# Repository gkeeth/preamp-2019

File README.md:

# preamp-2019

Balanced input & output preamplifier with volume and balance controls.

Based on preamps designed by Doug Self (see Small Signal Audio Design by Douglas Self)

The preamp is split over several PCBs, with a kicad project for each:
1. balanced_amplifier: balanced amplifier with volume/balance controls
2. power_supply: power supplies for
    - positive analog rail
    - negative analog rail
    - digital/relay rail
3. input_output_board: board with input/output jacks and relays to select the desired input
4. front_panel_board: board with input selection switch and headphone/main output switch
5. headphone_amp: a very basic headphone amplifier that converts the balanced
   output of the balanced_amplifier board to an unbalanced signal, and buffers it

This work is licensed under a [Creative Commons Attribution-ShareAlike 4.0
International License][cc-by-sa].

[![CC BY-SA 4.0][cc-by-sa-image]][cc-by-sa]

[cc-by-sa]: http://creativecommons.org/licenses/by-sa/4.0/
[cc-by-sa-image]: https://licensebuttons.net/l/by-sa/4.0/88x31.png
[cc-by-sa-shield]: https://img.shields.io/badge/License-CC%20BY--SA%204.0-lightgrey.svg

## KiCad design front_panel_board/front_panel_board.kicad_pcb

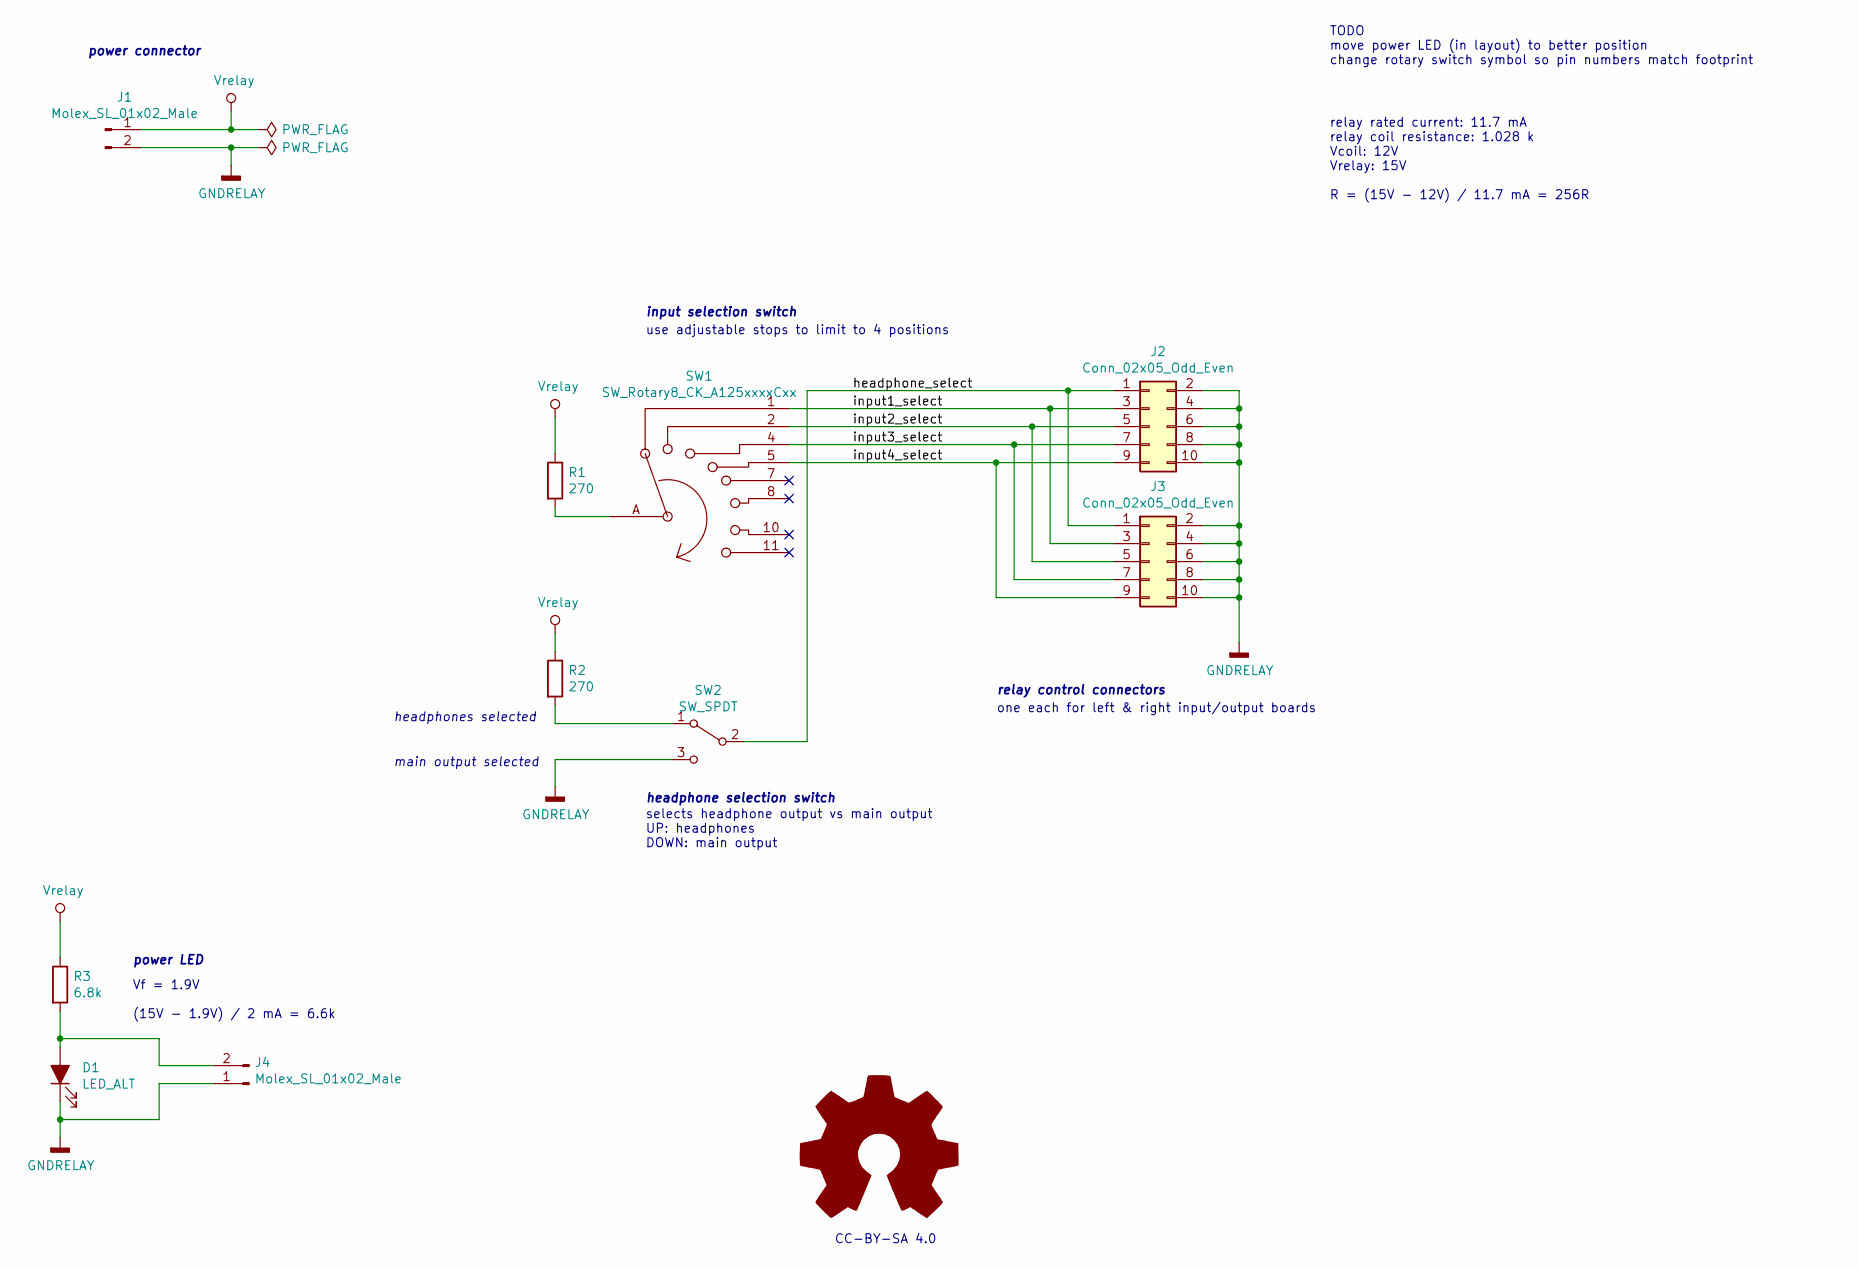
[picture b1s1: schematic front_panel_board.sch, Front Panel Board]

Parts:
D1: LED_ALT; LED_D5.0mm; Manufacturer PN WP7113LGD
J1, J4: Molex_SL_01x02_Male; Molex_SL_A-70543-0001_1x02_P2.54mm_Vertical; Manufacturer PN 0705430001
J2, J3: Conn_02x05_Odd_Even; Molex_C-Grid_70246-1001_2x05_P2.54mm_Vertical; Manufacturer PN 0702461001
R1, R2: 270; R_0805_2012Metric_Pad1.15x1.40mm_HandSolder; Manufacturer PN RT0805FRE07270RL
R3: 6.8k; R_0603_1608Metric_Pad1.05x0.95mm_HandSolder; Manufacturer PN YAG5968CT-ND
SW1: SW_Rotary8_CK_A125xxxxCxx; Manufacturer PN A12505RNCQ
SW2: SW_SPDT; SW_Toggle_SPDT_NKK_M201xxxx03; Manufacturer PN M2012SS1W03

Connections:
/headphone_select: J2.1, J3.1, SW2.2 (B)
/input1_select: J2.3, J3.3, SW1.1
/input2_select: J2.5, J3.5, SW1.2
/input3_select: J2.7, J3.7, SW1.4
/input4_select: J2.9, J3.9, SW1.5
GNDRELAY: D1.1 (K), J1.2, J2.2, J2.4, J2.6, J2.8, J2.10, J3.2, J3.4, J3.6, J3.8, J3.10, J4.1, SW2.3 (C)
unnamed: D1.2 (A), J4.2, R3.2
unnamed: R1.2, SW1.A
unnamed: R2.2, SW2.1 (A)
Vrelay: J1.1, R1.1, R2.1, R3.1

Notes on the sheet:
selects headphone output vs main output UP: headphones DOWN: main output
headphone selection switch
input selection switch
power connector
power LED
use adjustable stops to limit to 4 positions
relay rated current: 11.7 mA relay coil resistance: 1.028 k Vcoil: 12V Vrelay: 15V R = (15V - 12V) / 11.7 mA = 256R
Vf = 1.9V (15V - 1.9V) / 2 mA = 6.6k
TODO move power LED (in layout) to better position change rotary switch symbol so pin numbers match footprint
CC-BY-SA 4.0
relay control connectors
one each for left & right input/output boards
headphones selected
main output selected

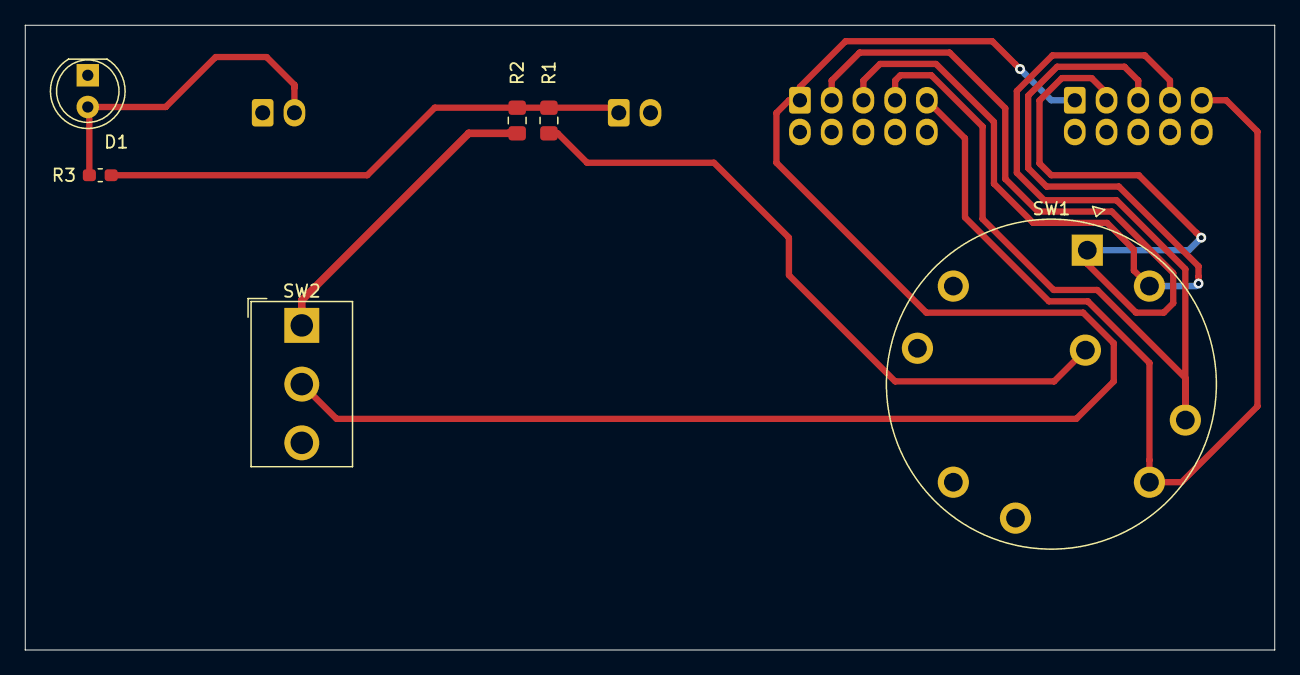
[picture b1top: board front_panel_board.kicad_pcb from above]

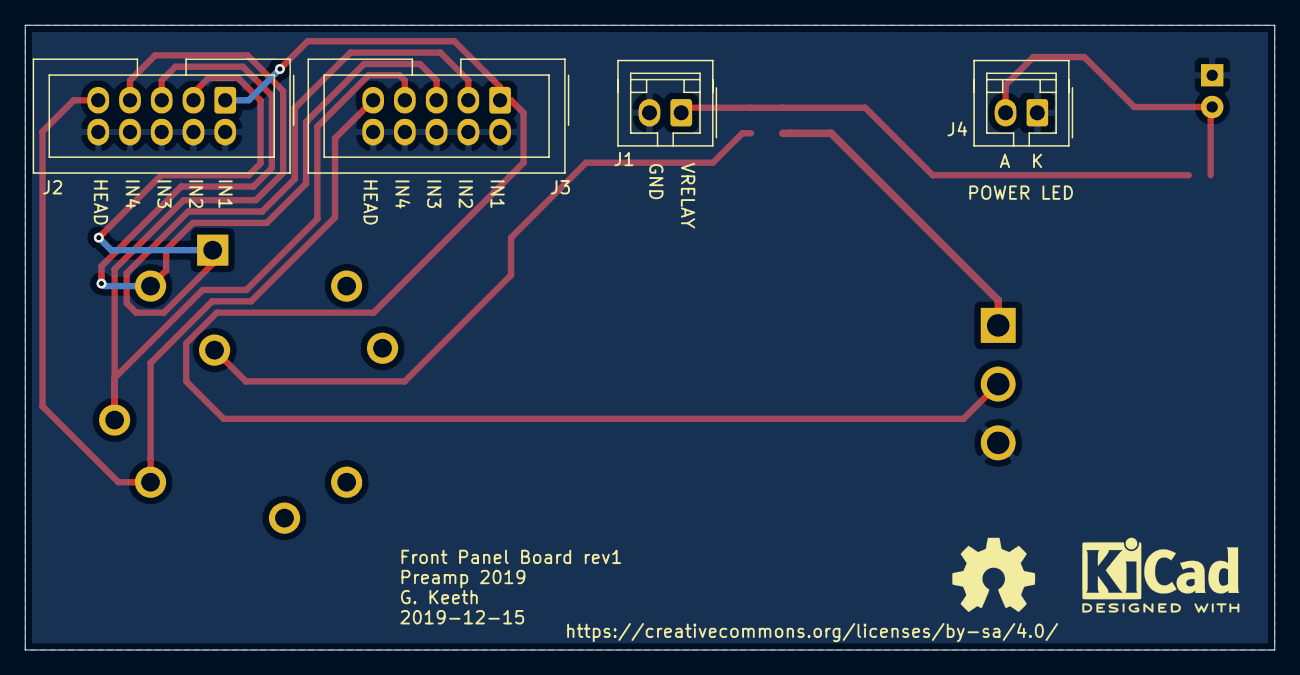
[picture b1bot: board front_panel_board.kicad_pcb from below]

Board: 2 copper layers, 100.0 x 50.0 mm, 10 parts (4 on the bottom side), 10 nets.

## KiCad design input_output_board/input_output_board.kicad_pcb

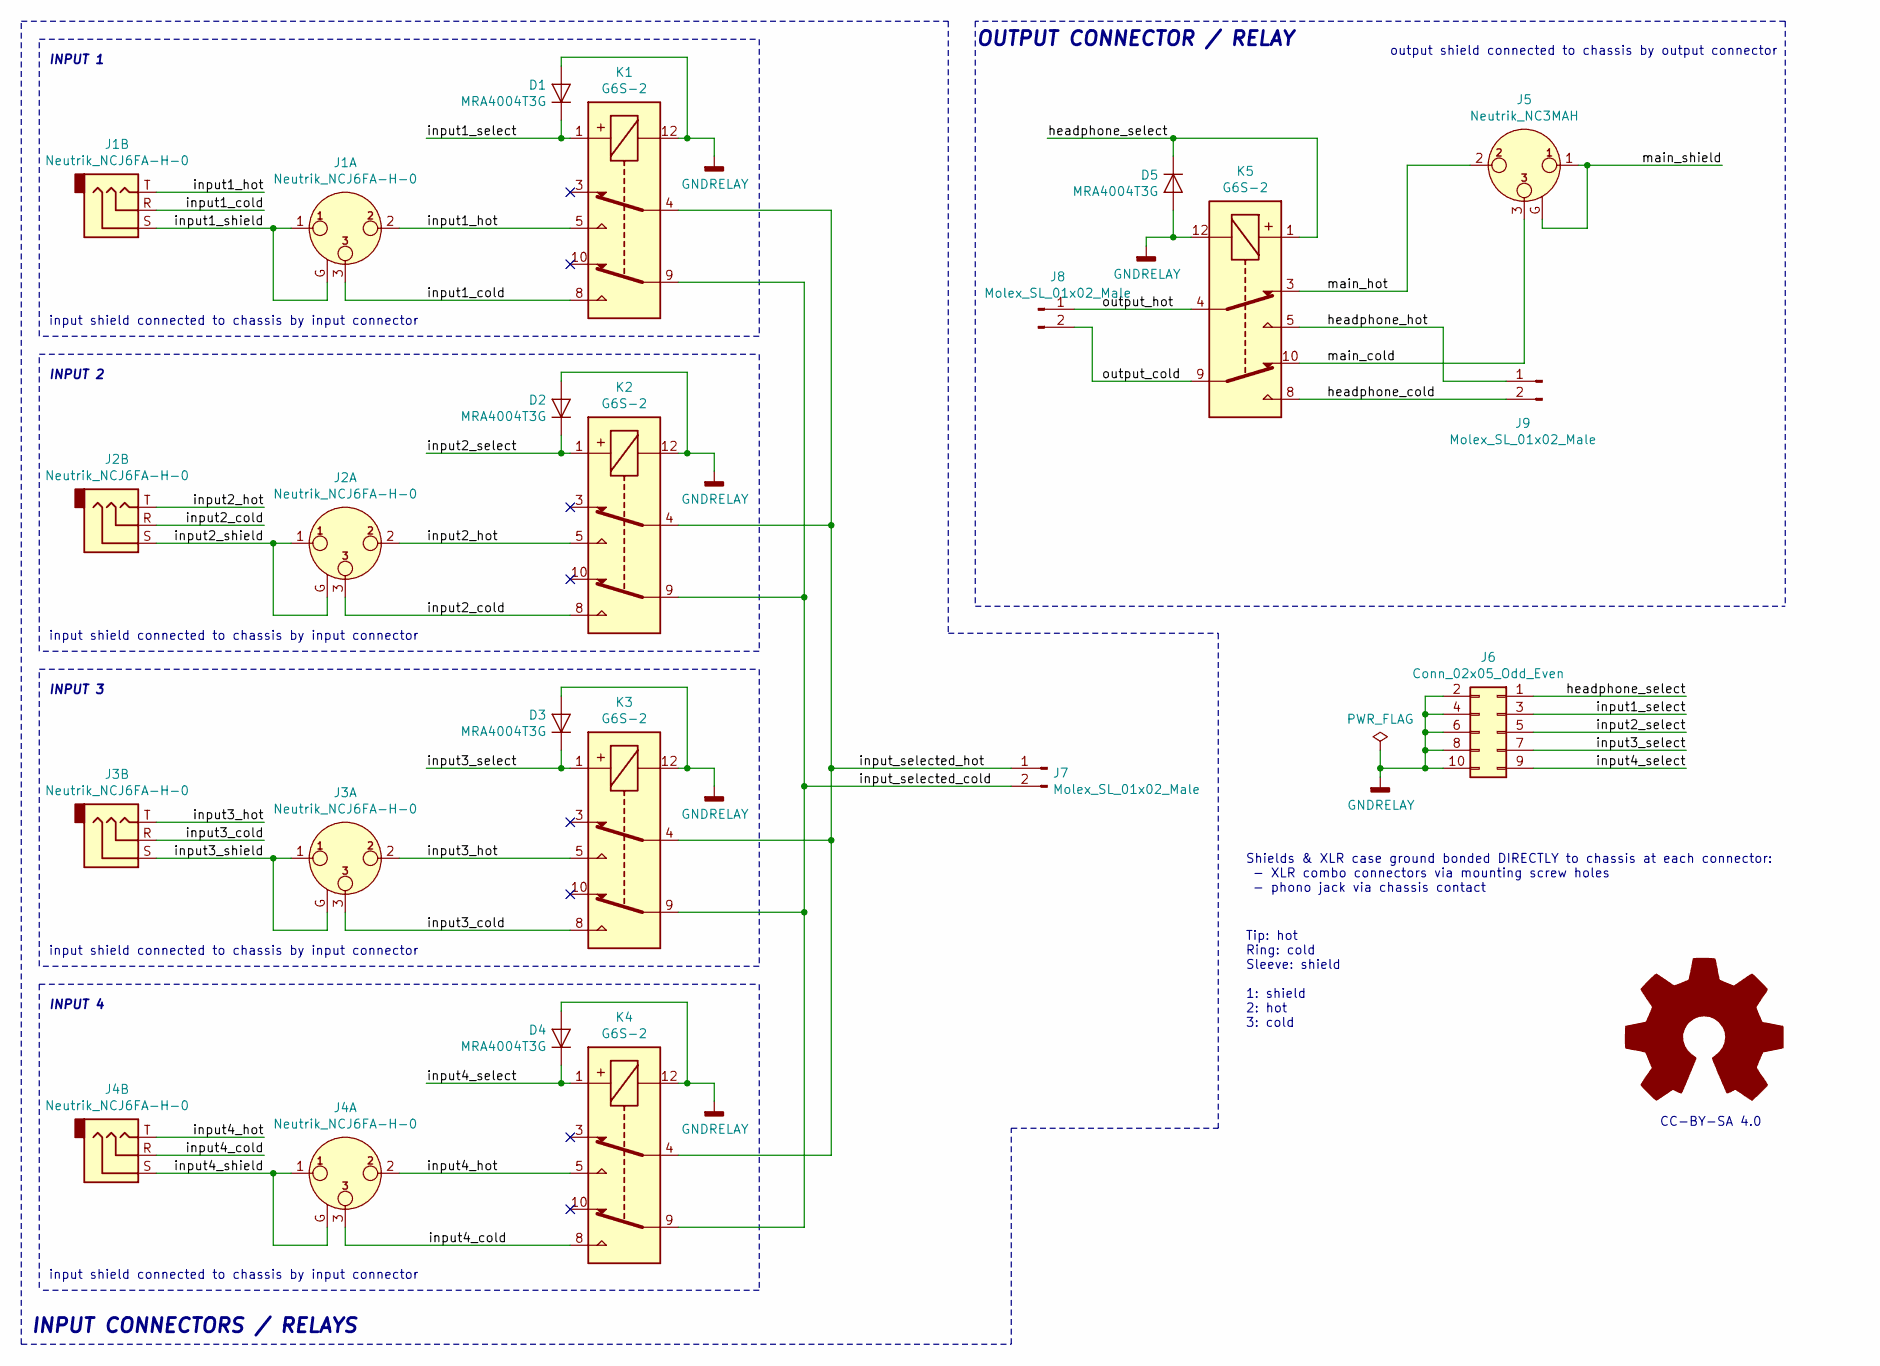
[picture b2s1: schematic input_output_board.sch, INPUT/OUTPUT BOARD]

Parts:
D1, D2, D3, D4, D5: MRA4004T3G; D_SMA; Manufacturer PN MRA4004T3G
J1, J2, J3, J4: Neutrik_NCJ6FA-H-0; Jack_XLR-6.35mm_Neutrik_NCJ6FA-H-0_Horizontal; Manufacturer PN NCJ6FA-H-0
J5: Neutrik_NC3MAH; Jack_XLR_Neutrik_NC3MAH_Horizontal; Manufacturer PN NC3MAH
J6: Conn_02x05_Odd_Even; Molex_C-Grid_70247-10xx_2x05_P2.54mm_Horizontal; Manufacturer PN 0702461001
J7, J8, J9: Molex_SL_01x02_Male; Molex_SL_A-70553-0001_1x02_P2.54mm_Horizontal; Manufacturer PN 0705430001
K1, K2, K3, K4, K5: G6S-2; Relay_DPDT_Omron_G6S-2F; Manufacturer PN G6S-2F DC12

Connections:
/headphone_cold: J9.2, K5.8
/headphone_hot: J9.1, K5.5
/headphone_select: D5.1 (K), J6.1, K5.1
/input1_cold: J1.3, J1.R, K1.8
/input1_hot: J1.2, J1.T, K1.5
/input1_select: D1.1 (K), J6.3, K1.1
/input1_shield: J1.1, J1.G, J1.S
/input2_cold: J2.3, J2.R, K2.8
/input2_hot: J2.2, J2.T, K2.5
/input2_select: D2.1 (K), J6.5, K2.1
/input2_shield: J2.1, J2.G, J2.S
/input3_cold: J3.3, J3.R, K3.8
/input3_hot: J3.2, J3.T, K3.5
/input3_select: D3.1 (K), J6.7, K3.1
/input3_shield: J3.1, J3.G, J3.S
/input4_cold: J4.3, J4.R, K4.8
/input4_hot: J4.2, J4.T, K4.5
/input4_select: D4.1 (K), J6.9, K4.1
/input4_shield: J4.1, J4.G, J4.S
/input_selected_cold: J7.2, K1.9, K2.9, K3.9, K4.9
/input_selected_hot: J7.1, K1.4, K2.4, K3.4, K4.4
/main_cold: J5.3, K5.10
/main_hot: J5.2, K5.3
/main_shield: J5.1, J5.G
/output_cold: J8.2, K5.9
/output_hot: J8.1, K5.4
GNDRELAY: D1.2 (A), D2.2 (A), D3.2 (A), D4.2 (A), D5.2 (A), J6.2, J6.4, J6.6, J6.8, J6.10, K1.12, K2.12, K3.12, K4.12, K5.12

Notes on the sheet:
Tip: hot Ring: cold Sleeve: shield 1: shield 2: hot 3: cold
Shields & XLR case ground bonded DIRECTLY to chassis at each connector: - XLR combo connectors via mounting screw holes - phono jack via chassis contact
INPUT CONNECTORS / RELAYS
INPUT 1
INPUT 2
INPUT 3
INPUT 4
CC-BY-SA 4.0
input shield connected to chassis by input connector
output shield connected to chassis by output connector
OUTPUT CONNECTOR / RELAY

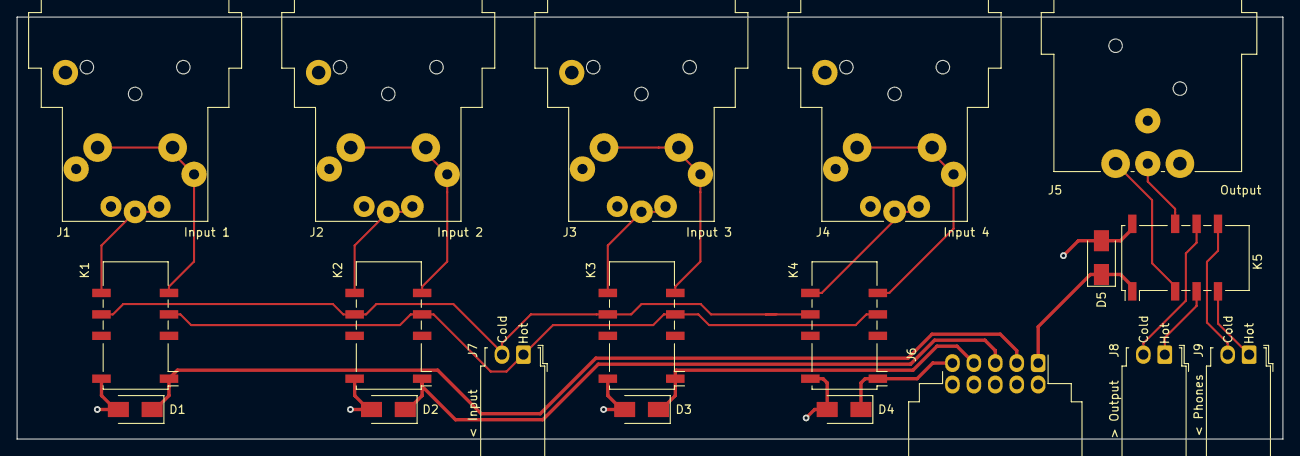
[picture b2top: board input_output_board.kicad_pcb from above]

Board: 2 copper layers, 150.0 x 50.0 mm, 19 parts (0 on the bottom side), 27 nets.

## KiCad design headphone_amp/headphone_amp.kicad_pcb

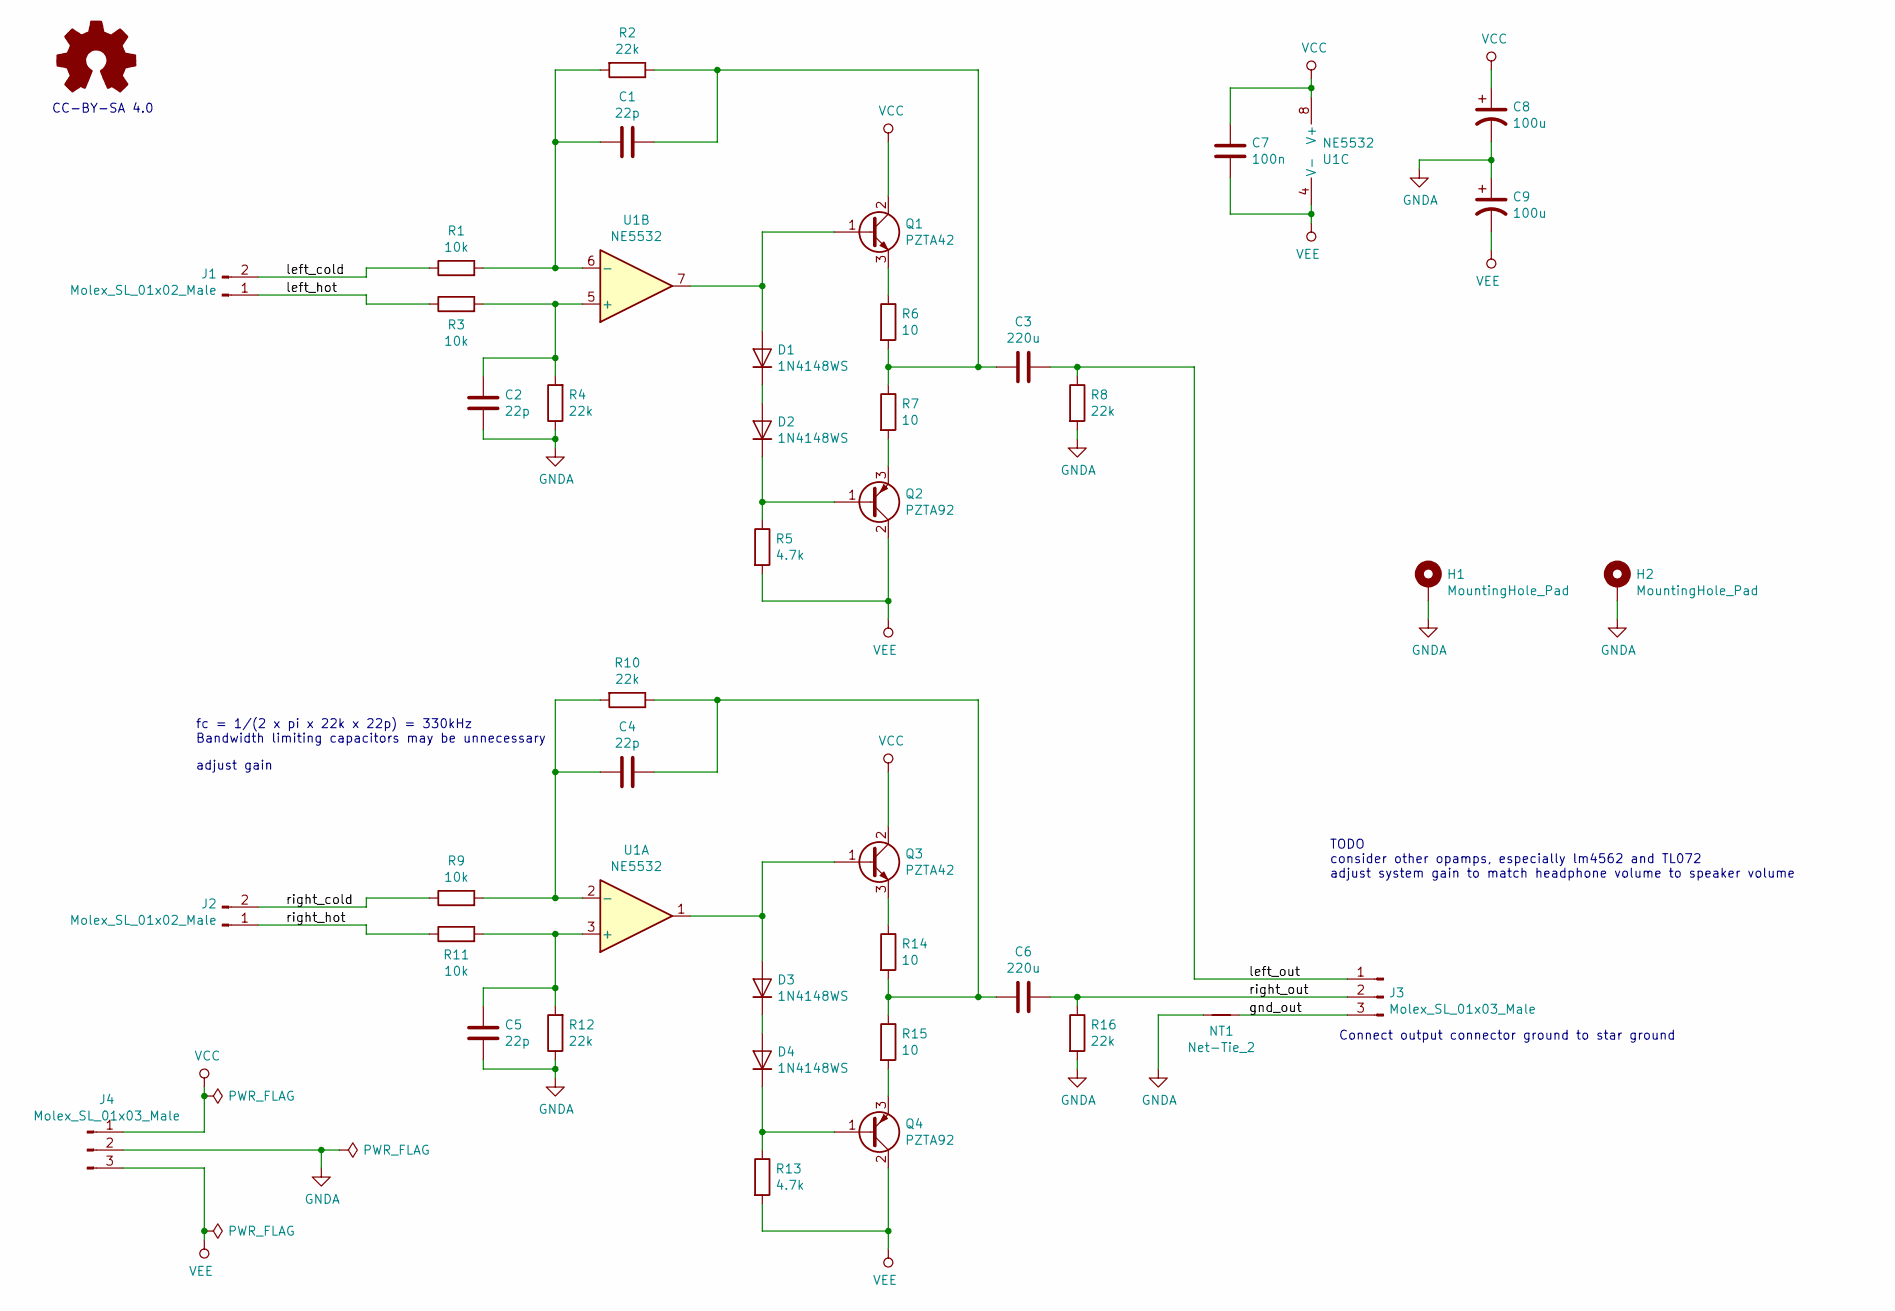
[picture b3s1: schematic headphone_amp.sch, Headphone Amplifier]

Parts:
C1, C2, C4, C5: 22p; C_0603_1608Metric_Pad1.05x0.95mm_HandSolder; Manufacturer PN C0603C220J5GAC7411
C3, C6: 220u; C_Radial_D12.5mm_H20.0mm_P5.00mm; Voltage Rating 35V; Manufacturer PN UVP1V221MHD
C7: 100n; C_0805_2012Metric_Pad1.15x1.40mm_HandSolder; Manufacturer PN GCM21BR72A104KA37K
C8, C9: 100u; CP_Radial_D6.3mm_P2.50mm; Voltage Rating 35V; Manufacturer PN UVR1V101MED
D1, D2, D3, D4: 1N4148WS; D_SOD-323; Manufacturer PN 1N4148WS
H1, H2: MountingHole_Pad; MountingHole_3.2mm_M3_Pad
J1, J2: Molex_SL_01x02_Male; Molex_SL_A-70553-0001_1x02_P2.54mm_Horizontal; Manufacturer PN 70553-0001
J3, J4: Molex_SL_01x03_Male; Molex_SL_A-70553-0002_1x03_P2.54mm_Horizontal; Manufacturer PN 70553-0002
NT1: Net-Tie_2; NetTie-2_SMD_Pad2.0mm
Q1, Q3: PZTA42; SOT-223-3_TabPin2; Manufacturer PN PZTA42T1G
Q2, Q4: PZTA92; SOT-223-3_TabPin2; Manufacturer PN PZTA92T1G
R1, R3, R9, R11: 10k; R_0603_1608Metric_Pad1.05x0.95mm_HandSolder; Manufacturer PN RT0603FRE0710KL
R2, R4, R8, R10, R12, R16: 22k; R_0603_1608Metric_Pad1.05x0.95mm_HandSolder; Manufacturer PN RT0603FRE1322KL
R5, R13: 4.7k; R_0603_1608Metric_Pad1.05x0.95mm_HandSolder; Manufacturer PN RT0603FRE074K7L
R6, R7, R14, R15: 10; R_0603_1608Metric_Pad1.05x0.95mm_HandSolder; Manufacturer PN RNCP0603FTD10R0
U1: NE5532; SOIC-8_3.9x4.9mm_P1.27mm; Manufacturer PN NE5532AD8R2G

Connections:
/gnd_out: J3.3, NT1.2
/left_cold: J1.2, R1.1
/left_hot: J1.1, R3.1
/left_out: C3.1, J3.1, R8.1
/right_cold: J2.2, R9.1
/right_hot: J2.1, R11.1
/right_out: C6.1, J3.2, R16.1
GNDA: C2.2, C5.2, C8.2, C9.1, H1.1, H2.1, J4.2, NT1.1, R4.1, R8.2, R12.1, R16.2
unnamed: C1.1, C3.2, R2.1, R6.2, R7.1
unnamed: C1.2, R1.2, R2.2, U1.6 (-)
unnamed: C2.1, R3.2, R4.2, U1.5 (+)
unnamed: C4.1, C6.2, R10.1, R14.2, R15.1
unnamed: C4.2, R9.2, R10.2, U1.2 (-)
unnamed: C5.1, R11.2, R12.2, U1.3 (+)
unnamed: D1.1 (K), D2.2 (A)
unnamed: D1.2 (A), Q1.1 (B), U1.7
unnamed: D2.1 (K), Q2.1 (B), R5.1
unnamed: D3.1 (K), D4.2 (A)
unnamed: D3.2 (A), Q3.1 (B), U1.1
unnamed: D4.1 (K), Q4.1 (B), R13.1
unnamed: Q1.3 (E), R6.1
unnamed: Q2.3 (E), R7.2
unnamed: Q3.3 (E), R14.1
unnamed: Q4.3 (E), R15.2
VCC: C7.1, C8.1, J4.1, Q1.2 (C), Q3.2 (C), U1.8 (V+)
VEE: C7.2, C9.2, J4.3, Q2.2 (C), Q4.2 (C), R5.2, R13.2, U1.4 (V-)

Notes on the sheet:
TODO consider other opamps, especially lm4562 and TL072 adjust system gain to match headphone volume to speaker volume
CC-BY-SA 4.0
fc = 1/(2 x pi x 22k x 22p) = 330kHz Bandwidth limiting capacitors may be unnecessary
Connect output connector ground to star ground
adjust gain

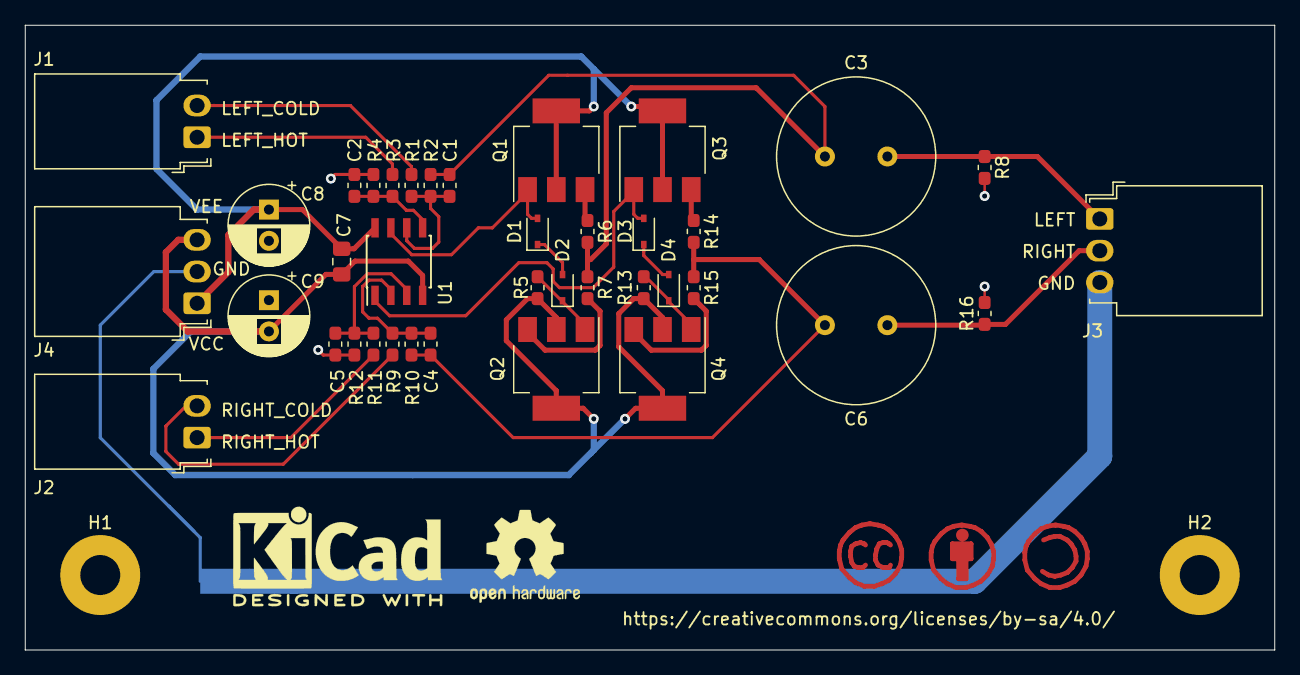
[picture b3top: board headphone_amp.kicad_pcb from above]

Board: 2 copper layers, 100.0 x 50.0 mm, 41 parts (1 on the bottom side), 26 nets.

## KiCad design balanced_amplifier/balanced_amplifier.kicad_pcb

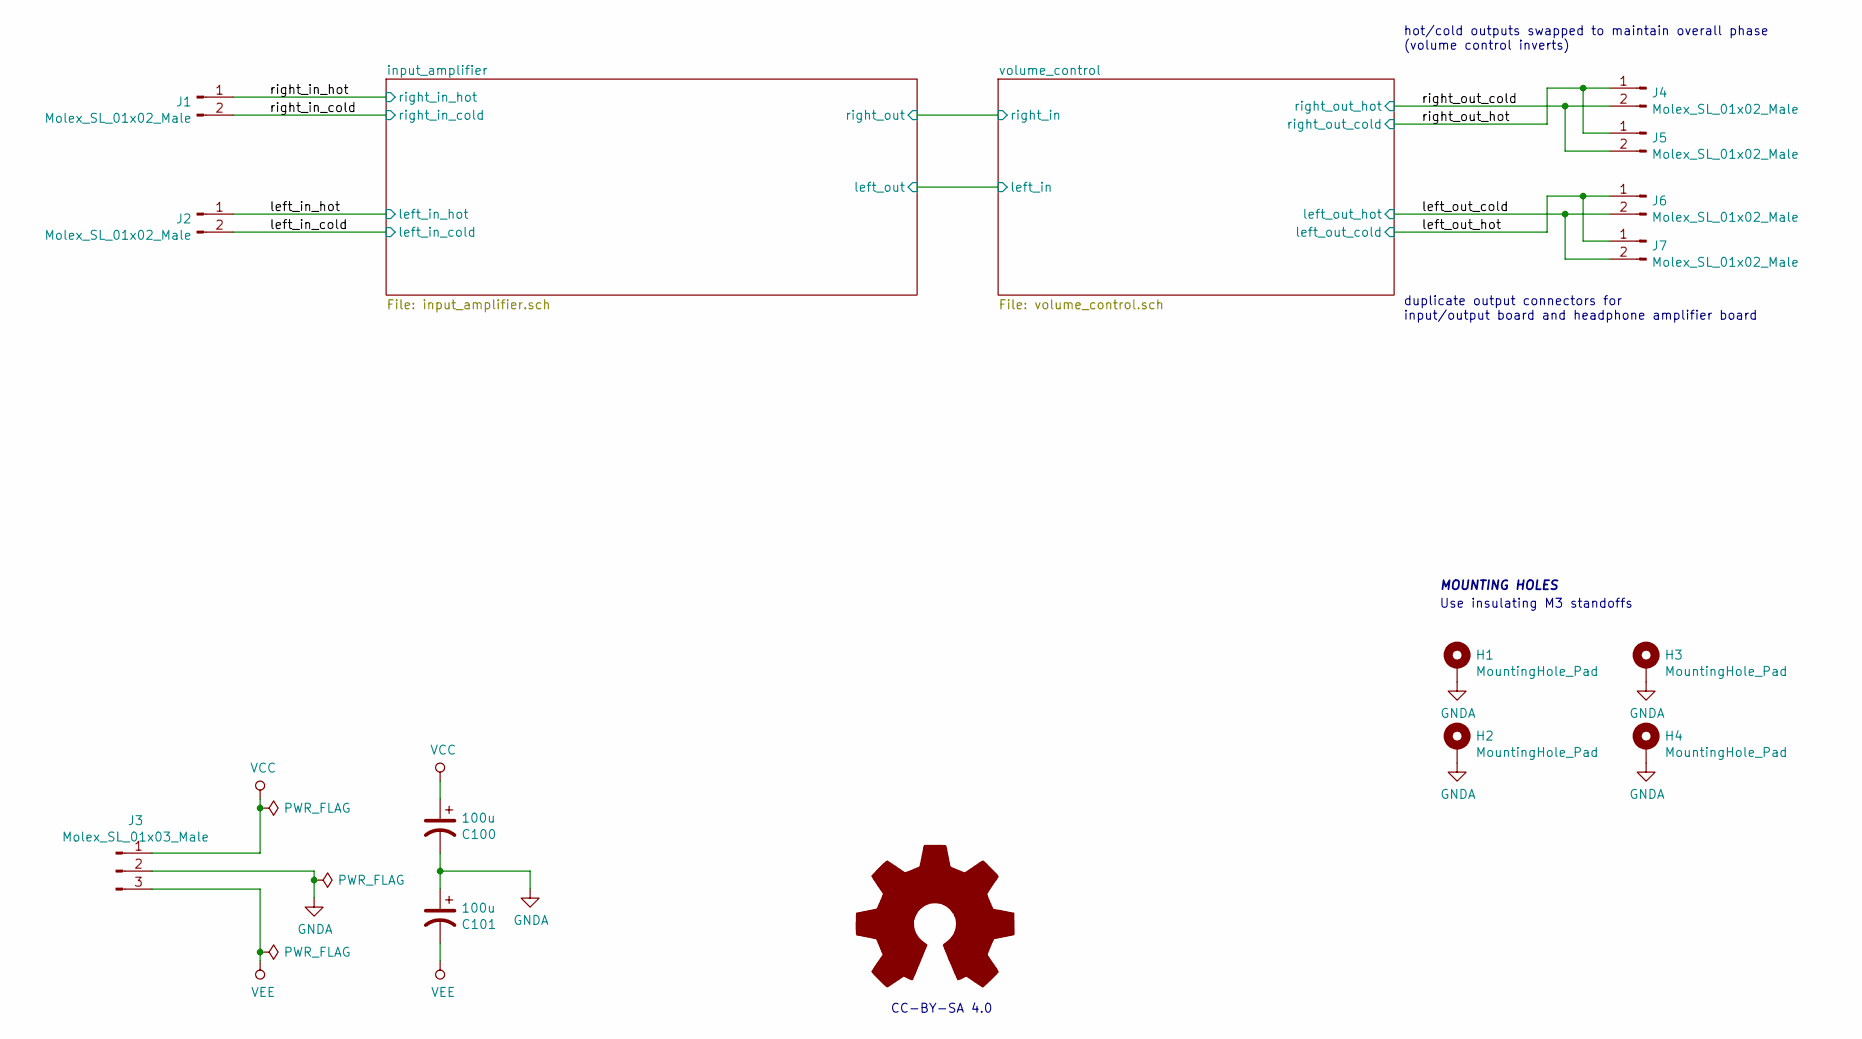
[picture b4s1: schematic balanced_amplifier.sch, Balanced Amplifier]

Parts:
C100, C101: 100u; CP_Radial_D6.3mm_P2.50mm; Voltage Rating 35V; Manufacturer PN UVR1V101MED
H1, H2, H3, H4: MountingHole_Pad; MountingHole_3.2mm_M3_Pad
J1, J2, J4, J5, J6, J7: Molex_SL_01x02_Male; Molex_SL_A-70543-0001_1x02_P2.54mm_Vertical; Manufacturer PN 0705430001
J3: Molex_SL_01x03_Male; Molex_SL_A-70543-0002_1x03_P2.54mm_Vertical; Manufacturer PN 0705430002

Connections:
/left_in_cold: J2.2; also elsewhere on the board
/left_in_hot: J2.1; also elsewhere on the board
/left_out_cold: J6.2, J7.2; also elsewhere on the board
/left_out_hot: J6.1, J7.1; also elsewhere on the board
/right_in_cold: J1.2; also elsewhere on the board
/right_in_hot: J1.1; also elsewhere on the board
/right_out_cold: J4.2, J5.2; also elsewhere on the board
/right_out_hot: J4.1, J5.1; also elsewhere on the board
GNDA: C100.2, C101.1, H1.1, H2.1, H3.1, H4.1, J3.2; also elsewhere on the board
VCC: C100.1, J3.1; also elsewhere on the board
VEE: C101.2, J3.3; also elsewhere on the board

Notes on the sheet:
hot/cold outputs swapped to maintain overall phase (volume control inverts)
Use insulating M3 standoffs
duplicate output connectors for input/output board and headphone amplifier board
MOUNTING HOLES
CC-BY-SA 4.0

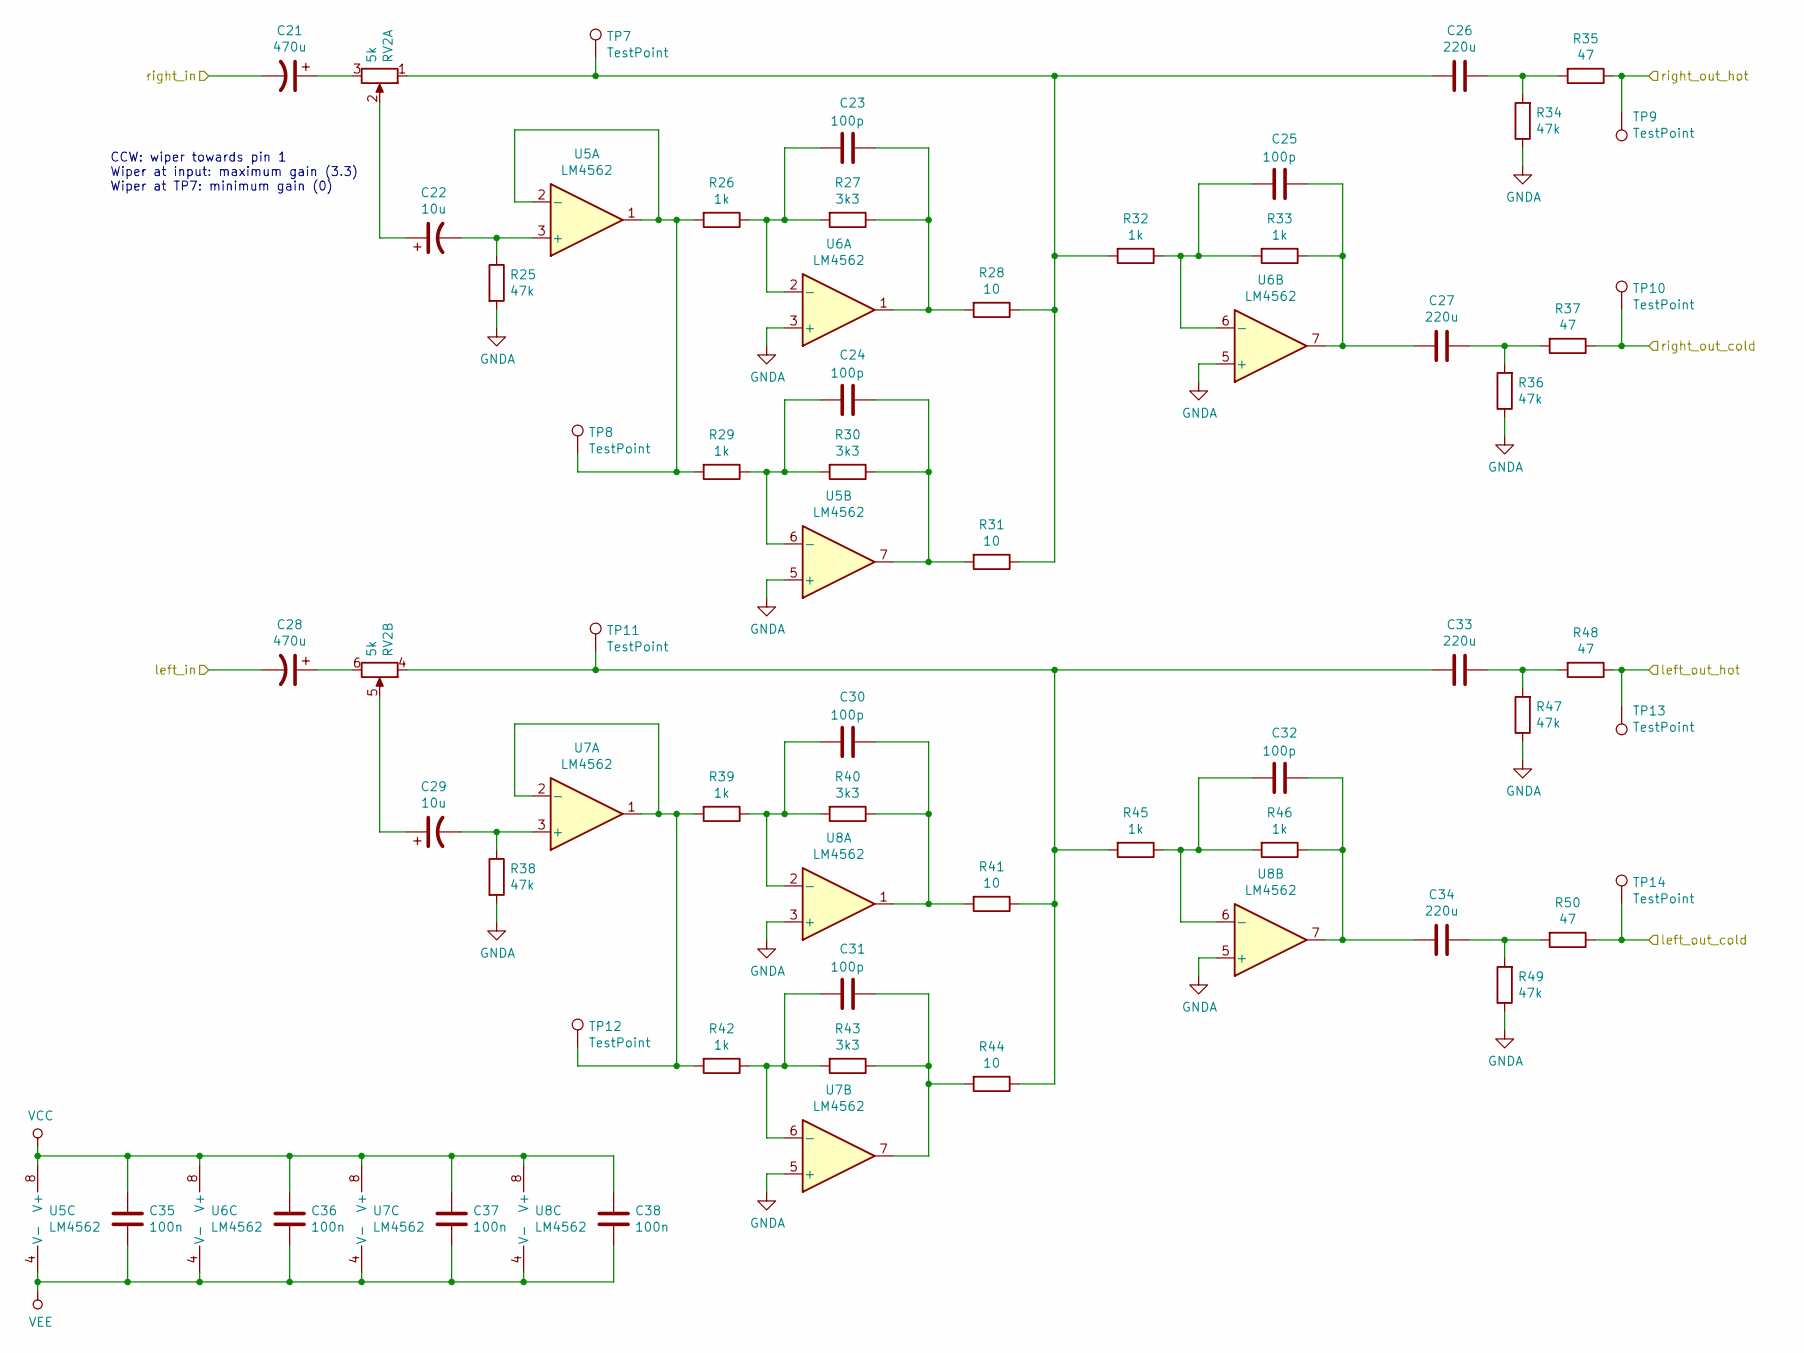
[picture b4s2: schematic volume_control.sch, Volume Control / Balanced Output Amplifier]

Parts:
C21, C28: 470u; CP_Radial_D10.0mm_P5.00mm; Voltage Rating 35V; Manufacturer PN UVR1V471MPD
C22, C29: 10u; CP_Radial_D5.0mm_P2.00mm; Voltage Rating 35V; Manufacturer PN UVR1V100MDD
C23, C24, C25, C30, C31, C32: 100p; C_0603_1608Metric_Pad1.05x0.95mm_HandSolder; Manufacturer PN CC0603JRNPO9BN101
C26, C27, C33, C34: 220u; C_Radial_D12.5mm_H20.0mm_P5.00mm; Voltage Rating 35V; Manufacturer PN UVP1V221MHD
C35, C36, C37, C38: 100n; C_0805_2012Metric_Pad1.15x1.40mm_HandSolder; Manufacturer PN GCM21BR72A104KA37K
R25, R34, R36, R38, R47, R49: 47k; R_0603_1608Metric_Pad1.05x0.95mm_HandSolder; Manufacturer PN RT0603FRE0747KL
R26, R29, R32, R33, R39, R42, R45, R46: 1k; R_1206_3216Metric_Pad1.42x1.75mm_HandSolder; Manufacturer PN RT1206FRE071KL
R27, R30, R40, R43: 3k3; R_0603_1608Metric_Pad1.05x0.95mm_HandSolder; Manufacturer PN RT0603FRE073K3L
R28, R31, R41, R44: 10; R_0603_1608Metric_Pad1.05x0.95mm_HandSolder; Manufacturer PN RNCP0603FTD10R0
R35, R37, R48, R50: 47; R_0603_1608Metric_Pad1.05x0.95mm_HandSolder; Manufacturer PN RT0603DRE0747RL
RV2: 5k; Potentiometer_Bourns_91A2x-x28-xxx_Dual_Horizontal; Manufacturer PN 91A2A-B28-B13/B13L
TP7, TP8, TP9, TP10, TP11, TP12, TP13, TP14: TestPoint; TestPoint_Keystone_5000-5004_Miniature; Manufacturer PN 5002
U5, U6, U7, U8: LM4562; SOIC-8_3.9x4.9mm_P1.27mm; Manufacturer PN LM4562MAX/NOPB

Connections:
/left_out_cold: R48.1, TP13.1; also elsewhere on the board
/left_out_hot: R50.1, TP14.1; also elsewhere on the board
/right_out_cold: R35.1, TP9.1; also elsewhere on the board
/right_out_hot: R37.1, TP10.1; also elsewhere on the board
/volume_control/left_in: C28.2; also elsewhere on the board
/volume_control/right_in: C21.2; also elsewhere on the board
GNDA: R25.2, R34.1, R36.1, R38.2, R47.1, R49.1, U5.5 (+), U6.3 (+), U6.5 (+), U7.5 (+), U8.3 (+), U8.5 (+); also elsewhere on the board
unnamed: C21.1, RV2.3
unnamed: C22.1, RV2.2
unnamed: C22.2, R25.1, U5.3 (+)
unnamed: C23.1, R27.1, R28.2, U6.1
unnamed: C23.2, R26.1, R27.2, U6.2 (-)
unnamed: C24.1, R30.1, R31.2, U5.7
unnamed: C24.2, R29.1, R30.2, U5.6 (-)
unnamed: C25.1, C27.2, R33.1, U6.7
unnamed: C25.2, R32.1, R33.2, U6.6 (-)
unnamed: C26.1, R34.2, R35.2
unnamed: C26.2, R28.1, R31.1, R32.2, RV2.1, TP7.1
unnamed: C27.1, R36.2, R37.2
unnamed: C28.1, RV2.6
unnamed: C29.1, RV2.5
unnamed: C29.2, R38.1, U7.3 (+)
unnamed: C30.1, R40.1, R41.2, U8.1
unnamed: C30.2, R39.1, R40.2, U8.2 (-)
unnamed: C31.1, R43.1, R44.2, U7.7
unnamed: C31.2, R42.1, R43.2, U7.6 (-)
unnamed: C32.1, C34.2, R46.1, U8.7
unnamed: C32.2, R45.1, R46.2, U8.6 (-)
unnamed: C33.1, R47.2, R48.2
unnamed: C33.2, R41.1, R44.1, R45.2, RV2.4, TP11.1
unnamed: C34.1, R49.2, R50.2
unnamed: R26.2, R29.2, TP8.1, U5.1, U5.2 (-)
unnamed: R39.2, R42.2, TP12.1, U7.1, U7.2 (-)
VCC: C35.1, C36.1, C37.1, C38.1, U5.8 (V+), U6.8 (V+), U7.8 (V+), U8.8 (V+); also elsewhere on the board
VEE: C35.2, C36.2, C37.2, C38.2, U5.4 (V-), U6.4 (V-), U7.4 (V-), U8.4 (V-); also elsewhere on the board

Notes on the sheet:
CCW: wiper towards pin 1 Wiper at input: maximum gain (3.3) Wiper at TP7: minimum gain (0)

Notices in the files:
balanced_amplifier/balanced_amplifier.kicad_pcb:
https://creativecommons.org/licenses/by-sa/4.0
